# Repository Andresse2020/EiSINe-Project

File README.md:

# Raspberry Pi License Plate Detection System

Real-time license plate detection system for Raspberry Pi with camera support. Detects license plates using YOLO, designed with a clean layered architecture for easy maintenance and hardware portability.

---

## 📑 Table of Contents

- [Project Overview](#-project-overview)
- [Current Status](#-current-status)
- [Architecture](#️-architecture)
- [Project Structure](#-project-structure)
- [Installation](#-installation)
- [Configuration](#️-configuration)
- [Usage](#-usage)
- [Key Components](#-key-components-explained)
- [Development Guidelines](#️-development-guidelines)
- [Testing](#-testing)
- [Troubleshooting](#-troubleshooting)
- [Requirements](#-requirements-summary)
- [Roadmap](#️-roadmap)
- [Contributing](#-contributing)
- [License](#-license)

---

## 🎯 Project Overview

This system captures video frames from a camera, detects license plates in real-time using YOLO object detection, and provides a foundation for future OCR integration. The architecture is designed to run identically on both **PC (development)** and **Raspberry Pi (production)** by simply changing a configuration parameter.

### Key Features

- **Real-time detection**: YOLO-based license plate detection with confidence scoring
- **Hardware abstraction**: Same code runs on PC and Raspberry Pi
- **Multi-driver support**: Easy camera backend switching via factory pattern
- **Thread-safe processing**: Concurrent frame capture and analysis
- **Headless compatible**: No display required for production deployment
- **Modular architecture**: Clean separation of concerns across layers

---

## ✅ Current Status

### Implemented

- ✅ **License plate detection** (YOLO-based object detection)
- ✅ **Multi-driver camera abstraction** (OpenCV implemented, Picamera2 ready)
- ✅ **Service-oriented architecture** (Service → Control → App)
- ✅ **Thread-safe frame processing pipeline**
- ✅ **Bounding box visualization** with confidence scores
- ✅ **Frame buffering service** for non-blocking capture
- ✅ **ROI extraction service** (foundation for plate cropping)
- ✅ **Preprocessing service** (image enhancement pipeline)

### Not Yet Implemented

- ⏳ **OCR** (Optical Character Recognition for reading plate text)
- ⏳ **Plate extraction refinement** (precise plate cropping)
- ⏳ **Database/logging system** (result persistence)
- ⏳ **Web interface** (remote monitoring dashboard)
- ⏳ **Picamera2 driver** (native Raspberry Pi Camera Module support)

---

## 🏗️ Architecture

### Layered Architecture Diagram

```
┌─────────────────────────────────────────────────────────────────────┐
│                           APP LAYER                                 │
│                           main.py                                   │
│               (User interface, display logic, entry point)          │
└────────────────────────────┬────────────────────────────────────────┘
                             │
┌────────────────────────────▼────────────────────────────────────────┐
│                         CONTROL LAYER                               │
│                        lpd_control.py                               │
│          (Pipeline orchestration, threading, business workflow)     │
└────────────────────────────┬────────────────────────────────────────┘
                             │
┌────────────────────────────▼────────────────────────────────────────┐
│                         SERVICE LAYER                               │
│  ┌──────────────────┐  ┌──────────────────┐  ┌──────────────────┐   │
│  │  Camera Service  │  │ YOLO Detector    │  │  Preprocess      │   │
│  │  (Frame buffer)  │  │ Service          │  │  Service         │   │
│  └──────────────────┘  └──────────────────┘  └──────────────────┘   │
│  ┌──────────────────┐  ┌──────────────────┐                         │
│  │ ROI Extraction   │  │  OCR Service     │                         │
│  │ Service          │  │  (Future)        │                         │
│  └──────────────────┘  └──────────────────┘                         │
│         (Reusable components: ML, image processing, I/O)            │
└────────────────────────────┬────────────────────────────────────────┘
                             │
┌────────────────────────────▼────────────────────────────────────────┐
│                       INTERFACE LAYER                               │
│                    camera_interface.py (ABC)                        │
│          (Abstract contract defining camera driver behavior)        │
└────────────────────────────┬────────────────────────────────────────┘
                             │
               ┌─────────────┴─────────────┐
               │                           │
 ┌─────────────▼──────────┐    ┌───────────▼──────────┐
 │   DRIVER LAYER         │    │   DRIVER LAYER       │
 │  opencv_camera.py      │    │  picamera2_camera.py │
 │  (USB/CSI via V4L2)    │    │  (Pi CSI - Future)   │
 │  Cross-platform        │    │  Native Raspberry Pi │
 └────────────────────────┘    └──────────────────────┘

┌─────────────────────────────────────────────────────────────────────┐
│                         CONFIG LAYER                                │
│                      camera_factory.py                              │
│          (Runtime driver selection and instantiation)               │
└─────────────────────────────────────────────────────────────────────┘
```

### Data Flow Pipeline

```
┌──────────────┐   ┌────────────────┐   ┌────────────────┐   ┌──────────┐
│   Camera     │──▶│    Camera      │──▶│      LPD       │──▶│   App    │
│   Driver     │   │    Service     │   │    Control     │   │  Layer   │
└──────────────┘   └────────────────┘   └────────────────┘   └──────────┘
      │                   │                     │                   │
  Hardware           Frame Buffer          YOLO Pipeline        Display
  Capture            (Thread-safe)         • Detection           Results
  (cv2.read)         • Latest frame        • ROI Extract
                     • Non-blocking        • Preprocess
                                          • Overlay
```

**Detailed Flow:**

1. **Camera Driver** (`opencv_camera.py`)
   - Captures raw frames from hardware via OpenCV
   - Returns normalized `Frame` objects

2. **Camera Service** (`camera_service.py`)
   - Runs background thread for continuous capture
   - Buffers latest frame in thread-safe manner
   - Converts `Frame` → `ImageFrame` for upper layers

3. **LPD Control** (`lpd_control.py`)
   - Pulls frames from Camera Service (non-blocking)
   - Runs detection pipeline:
     - YOLO detection → bounding boxes + confidence
     - ROI extraction (optional plate cropping)
     - Preprocessing (optional image enhancement)
     - Debug overlay rendering
   - Stores results thread-safely

4. **App Layer** (`main.py`)
   - Retrieves latest detection results
   - Displays frames with overlays
   - Handles user input (quit, pause, etc.)

---

## 📁 Project Structure

```
raspberry-lpd/
│
├── Software/
│   │
│   ├── App/
│   │   └── main.py                          # Application entry point
│   │
│   ├── Control/
│   │   └── lpd_control.py                   # Detection pipeline controller
│   │
│   ├── Service/
│   │   ├── camera_service.py                # Frame buffering service
│   │   ├── yolo_detector_service.py         # YOLO inference wrapper
│   │   ├── roi_extraction_service.py        # Plate region extraction
│   │   ├── plate_preprocess_service.py      # Image preprocessing
│   │   ├── ocr_service.py                   # OCR (placeholder)
│   │   └── ML_Models/
│   │       ├── license_plate_detector.pt    # YOLO weights (required)
│   │       └── yolov8n.pt                   # Optional backup model
│   │
│   ├── Interface/
│   │   └── camera_interface.py              # Abstract camera contract (ABC)
│   │
│   ├── Drivers/
│   │   └── opencv_camera.py                 # OpenCV camera implementation
│   │
│   ├── Config/
│   │   └── camera_factory.py                # Driver selection factory
│   │
│   ├── Tests/
│   │   ├── test_camera.py                   # Driver unit tests
│   │   └── test_camera_service.py           # Service layer tests
│   │
│   └── Tools/
│       └── debug_display.py                 # Debugging utilities
│
├── launch.sh                                # Startup script (source to load aliases)
├── setup.py                                 # Package configuration
└── README.md                                # This file
```

### Directory Responsibilities

| Directory | Purpose |
|-----------|---------|
| `App/` | User-facing application logic, entry points |
| `Control/` | Business workflows, pipeline orchestration |
| `Service/` | Reusable components (ML models, image processing, I/O) |
| `Interface/` | Abstract contracts for hardware abstraction |
| `Drivers/` | Concrete hardware implementations |
| `Config/` | Configuration files, factory patterns |
| `Tests/` | Unit and integration tests |
| `Tools/` | Development and debugging utilities |

---

## 🔧 Installation

### Development Environment (PC)

**Supported OS:** Linux, macOS, Windows

```bash
# 1. Clone repository
git clone https://github.com/Andresse2020/EiSINe-Project
cd EiSINe-Project

# 2. Ensure pip is installed
python3 -m ensurepip --upgrade
python3 -m pip install --upgrade pip

# 3. Create virtual environment (recommended)
python3 -m venv venv
source venv/bin/activate          # Linux/macOS
# venv\Scripts\activate           # Windows

# 4. Install dependencies
pip install numpy
pip install opencv-python
pip install ultralytics           # YOLO

# 5. Verify installation
python3 -c "import cv2; print('OpenCV:', cv2.__version__)"
python3 -c "import ultralytics; print('YOLO: OK')"
```

### Production Environment (Raspberry Pi)

**Tested on:** Raspberry Pi OS (Bullseye/Bookworm)

```bash
# 1. Update system
sudo apt update && sudo apt upgrade -y

# 2. Install system dependencies
sudo apt install -y python3-opencv python3-pip

# 3. Install Python packages
pip3 install ultralytics numpy

# Optional: Enable Raspberry Pi Camera Module (CSI)
sudo apt install -y python3-picamera2

# 4. Clone repository
git clone https://github.com/Andresse2020/EiSINe-Project
cd EiSINe-Project

# 5. Verify installation
python3 -c "import cv2; print('OpenCV:', cv2.__version__)"
```

### YOLO Model Setup

The system requires a trained YOLO model for license plate detection:

```bash
# Ensure the model file exists at:
Software/Service/ML_Models/license_plate_detector.pt

# If you need to train your own model, see:
# https://docs.ultralytics.com/modes/train/
```

---

## ⚙️ Configuration

### Camera Driver Selection

The **only** configuration needed to switch between PC and Raspberry Pi is in `Software/Config/camera_factory.py`:

```python
# ============================================================
# GLOBAL HARDWARE CONFIGURATION
# ============================================================

# Select active camera driver
# Options:
#   - "Software.Drivers.opencv_camera.OpenCVCamera"       (USB, V4L2)
#   - "Software.Drivers.picamera2_camera.Picamera2Camera" (Pi CSI - future)
ACTIVE_CAMERA_DRIVER = "Software.Drivers.opencv_camera.OpenCVCamera"

# Hardware parameters
CAMERA_HARDWARE_CONFIG = {
    "device_index": 0,                    # /dev/video0 (Linux) or index 0
    "default_resolution": (640, 480),     # Lower for Raspberry Pi performance
    "default_framerate": 30.0,            # FPS target
}
```

### Configuration Examples

#### For PC Development (USB Camera)
```python
ACTIVE_CAMERA_DRIVER = "Software.Drivers.opencv_camera.OpenCVCamera"
CAMERA_HARDWARE_CONFIG = {
    "device_index": 0,              # First USB camera
    "default_resolution": (1280, 720),
    "default_framerate": 30.0,
}
```

#### For Raspberry Pi (USB Camera)
```python
ACTIVE_CAMERA_DRIVER = "Software.Drivers.opencv_camera.OpenCVCamera"
CAMERA_HARDWARE_CONFIG = {
    "device_index": 0,              # /dev/video0
    "default_resolution": (640, 480),  # Lower resolution for performance
    "default_framerate": 15.0,         # Reduced FPS
}
```

#### For Raspberry Pi (CSI Camera - Future)
```python
ACTIVE_CAMERA_DRIVER = "Software.Drivers.picamera2_camera.Picamera2Camera"
CAMERA_HARDWARE_CONFIG = {
    "device_index": 0,
    "default_resolution": (1640, 1232),
    "default_framerate": 30.0,
}
```

---

## 🚀 Usage

### Basic Operation

```bash
# Method 1: Using launch script (loads aliases)
cd EiSINe-Project/Software
source launch.sh     # Once the launch.sh file is succefuly executed, you can run "run_app" and "show_video" in any directory.
run_app              # Launch main detection application
show_video           # Launch debug video display tool

# Method 2: Direct Python execution
cd EiSINe-Project
python3 -m Software.App.main
python3 -m Software.Tools.debug_display

# Method 3: From project root
cd EiSINe-Project
python3 -m Software.App.main
```

### Launch Script Details

The `launch.sh` script provides convenient aliases:

```bash
#!/bin/bash
# Load aliases into current shell
cd EiSINe-Project/Software
source launch.sh

# Available commands:
run_app      # Runs the license plate detection system
show_video   # Runs the debug video display utility
```

**Important:** Use `source launch.sh` (or `. launch.sh`) instead of `./launch.sh` to load aliases into your current shell session.

### Expected Console Output

```
🔍 [DebugDisplay] Starting viewer...
📡 CameraService started.
🧠 LPDControl started.

...

Press 'q' to quit
```

### Keyboard Controls

| Key | Action |
|-----|--------|
| `q` | Quit application |
| `p` | Pause/Resume detection |
| `s` | Save current frame |

### Running Tests

```bash
# Test camera driver
cd EiSINe-Project/Software
python3 -m Software.Tests.test_camera

# Test camera service
cd EiSINe-Project/Software
python3 -m Software.Tests.test_camera_service
```

---

## 🔍 Key Components Explained

### 1. `camera_interface.py` (Interface Layer)

**Purpose:** Defines the abstract contract that all camera drivers must implement.

**Key Methods:**
- `open(config)` — Initialize camera hardware
- `close()` — Release camera resources
- `start_stream()` — Begin continuous capture
- `stop_stream()` — End continuous capture
- `read(timeout)` — Capture a single frame
- `set_config(config)` — Apply camera settings (resolution, FPS, etc.)
- `capabilities()` — Query backend features

**Why it matters:** Upper layers only depend on this interface, never on concrete drivers.

---

### 2. `opencv_camera.py` (Driver Layer)

**Purpose:** Concrete implementation using OpenCV's `cv2.VideoCapture`.

**Features:**
- Works with USB cameras via V4L2 (Linux)
- Cross-platform support (Windows, macOS, Linux)
- Implements full `CameraInterface` contract
- Thread-safe frame acquisition

**Example Usage:**
```python
from Software.Drivers.opencv_camera import OpenCVCamera

cam = OpenCVCamera(device_index=0)
cam.open()
cam.start_stream()
frame = cam.read()  # Returns Frame object
cam.stop_stream()
cam.close()
```

---

### 3. `camera_service.py` (Service Layer)

**Purpose:** Provides thread-safe frame buffering with non-blocking access.

**Features:**
- Background thread continuously captures frames
- Stores latest frame in locked buffer
- Converts `Frame` → `ImageFrame` (simplified data structure)
- Non-blocking `get_latest()` method

**Why it matters:** Decouples frame capture from processing, preventing pipeline blocking.

**Example Usage:**
```python
from Software.Service.camera_service import CameraService

service = CameraService(camera_driver)
service.start()

# Non-blocking access
latest = service.get_latest()  # Returns ImageFrame or None
```

---

### 4. `yolo_detector_service.py` (Service Layer)

**Purpose:** Wraps YOLO model for license plate detection.

**Features:**
- Loads YOLO model from `.pt` file
- Runs inference on images
- Returns bounding boxes sorted by confidence

**Example Usage:**
```python
from Software.Service.yolo_detector_service import YoloDetectorService

detector = YoloDetectorService("path/to/model.pt")
detections = detector.detect(image)  # Returns [(x, y, w, h, conf), ...]
```

---

### 5. `lpd_control.py` (Control Layer)

**Purpose:** Orchestrates the complete detection pipeline.

**Pipeline Steps:**
1. Pull frame from Camera Service
2. Run YOLO detection
3. Extract ROI (optional)
4. Preprocess plate image (optional)
5. Draw debug overlay
6. Store results thread-safely

**Features:**
- Runs in background thread
- Thread-safe result storage
- Configurable processing steps

**Example Usage:**
```python
from Software.Control.lpd_control import LPDControl

controller = LPDControl(camera_service)
controller.start()

# Retrieve latest detection
result = controller.get_latest_result()  # { "bbox": (x,y,w,h), "confidence": 0.89, ... }
frame = controller.get_latest_frame()    # Processed frame with overlay
```

---

### 6. `camera_factory.py` (Config Layer)

**Purpose:** Centralized factory for driver instantiation.

**How it works:**
1. Reads `ACTIVE_CAMERA_DRIVER` from config
2. Dynamically imports driver class
3. Instantiates with `CAMERA_HARDWARE_CONFIG`
4. Validates implementation at runtime

**Example Usage:**
```python
from Software.Config.camera_factory import CameraFactory

# Returns concrete driver based on config
camera = CameraFactory.create()  # Returns OpenCVCamera or Picamera2Camera

# Upper layers only see CameraInterface
camera.open()
camera.start_stream()
```

**Why it matters:** Single source of truth for hardware selection. No conditional imports scattered across codebase.

---

## 🛠️ Development Guidelines

### Architecture Rules

1. **Never import drivers directly** — Always use `CameraFactory`
2. **Respect layer boundaries:**
   - App → Control → Service → Interface → Driver
   - Lower layers never import from upper layers
3. **Keep services stateless** or thread-safe
4. **No hardware logic** in Control/Service layers

### Adding a New Camera Driver

**Steps:**

1. Create `Software/Drivers/my_camera.py`
2. Inherit from `CameraInterface`
3. Implement all abstract methods
4. Update `camera_factory.py`
5. Write tests

**Example Template:**

```python
from Software.Interface.camera_interface import (
    CameraInterface,
    CameraConfig,
    Frame,
    CameraOpenError,
)

class MyCamera(CameraInterface):
    def __init__(self, device_index=0, **kwargs):
        super().__init__()
        self._device = device_index
        self._name = "MyCamera"

    def open(self, config=None):
        # Initialize hardware
        self._is_open = True

    def close(self):
        # Release hardware
        self._is_open = False

    def start_stream(self):
        self._is_streaming = True

    def stop_stream(self):
        self._is_streaming = False

    def read(self, timeout=2.0):
        # Capture and return Frame
        pass

    def flush(self):
        pass

    def capture(self, path=None):
        pass

    def set_config(self, config):
        pass

    def capabilities(self):
        return {}
```

### Adding a New Service

**Guidelines:**

1. Create `Software/Service/my_service.py`
2. Keep it stateless or use locks for thread safety
3. No direct hardware access (use existing services)
4. Write unit tests in `Software/Tests/`

**Example:**

```python
class MyService:
    def __init__(self):
        # Initialize resources
        pass

    def process(self, data):
        # Stateless processing
        return result
```

---

## 🧪 Testing

### Running Tests

```bash
# Run all tests
python3 -m pytest Software/Tests/ -v

# Run specific test file
python3 -m pytest Software/Tests/test_camera.py -v

# Run with coverage
pip install pytest-cov
python3 -m pytest Software/Tests/ --cov=Software --cov-report=html
```

### Manual Testing

```bash
# Test camera access
python3 -c "from Software.Config.camera_factory import CameraFactory; \
            cam = CameraFactory.create(); \
            cam.open(); \
            print('Camera OK')"

# Test YOLO model
python3 -c "from Software.Service.yolo_detector_service import YoloDetectorService; \
            detector = YoloDetectorService('Software/Service/ML_Models/license_plate_detector.pt'); \
            print('Model loaded OK')"
```

---

## 🐛 Troubleshooting

### Camera Not Detected

**Problem:** Camera fails to open

```bash
# Check available video devices
ls /dev/video*

# Test OpenCV access
python3 -c "import cv2; cap = cv2.VideoCapture(0); print('Opened:', cap.isOpened())"

# Check permissions
groups  # Should include 'video'
sudo usermod -a -G video $USER  # Add user to video group
# Logout and login again
```

### Low FPS on Raspberry Pi

**Solutions:**

1. **Reduce resolution:**
   ```python
   # In camera_factory.py
   "default_resolution": (320, 240),  # Even lower
   ```

2. **Lower framerate:**
   ```python
   "default_framerate": 10.0,
   ```

3. **Use lighter YOLO model:**
   - Replace `license_plate_detector.pt` with `yolov8n.pt` (nano version)

4. **Disable debug overlays:**
   ```python
   # In lpd_control.py, comment out:
   # self._draw_overlay(processed, x, y, w, h, conf)
   ```

### Permission Denied on `/dev/video0`

```bash
# Add user to video group
sudo usermod -a -G video $USER

# Or run with sudo (not recommended for production)
sudo python3 Software/App/main.py
```

### YOLO Model Not Found

```bash
# Check model path
ls Software/Service/ML_Models/license_plate_detector.pt

# If missing, download or train your own
# See: https://docs.ultralytics.com/
```

### Import Errors

```bash
# Ensure you're in project root
cd raspberry-lpd

# Check PYTHONPATH
export PYTHONPATH="${PYTHONPATH}:$(pwd)"

# Or install as package
pip install -e .
```

---

## 📦 Requirements Summary

### Hardware Requirements

| Component | Minimum | Recommended |
|-----------|---------|-------------|
| Raspberry Pi | Pi 3B | Pi 4 (4GB+) |
| Camera | USB 2.0 webcam | Pi Camera Module v2/v3 |
| RAM | 1GB | 2GB+ |
| SD Card | 8GB | 16GB+ (Class 10) |
| Power Supply | 2.5A | 3A (official) |

### Software Requirements

**Python:** 3.8 or higher

**Core Dependencies:**
- `opencv-python` (4.x) — Image processing and camera I/O
- `ultralytics` — YOLO object detection
- `numpy` — Numerical operations

**Optional Dependencies:**
- `picamera2` — Raspberry Pi Camera Module support (future)
- `pytest` — Unit testing
- `tesseract` / `easyocr` — OCR (future implementation)

### Operating Systems

| OS | Status |
|----|--------|
| Raspberry Pi OS (Bullseye/Bookworm) | ✅ Fully supported |
| Ubuntu 20.04+ | ✅ Supported |
| Debian 11+ | ✅ Supported |
| macOS | ⚠️ Development only |
| Windows 10+ | ⚠️ Development only |

---

## 🗺️ Roadmap

### Phase 1: Core Detection (Current)
- [x] YOLO-based license plate detection
- [x] OpenCV camera driver
- [x] Layered architecture
- [x] Thread-safe processing pipeline

### Phase 2: OCR Integration
- [ ] Implement OCR service (Tesseract or EasyOCR)
- [ ] Plate text extraction and validation
- [ ] Result confidence scoring
- [ ] Multi-language support

### Phase 3: Hardware Expansion
- [ ] Picamera2 driver for Raspberry Pi Camera Module
- [ ] Multi-camera support
- [ ] Hardware acceleration (Coral TPU, Neural Compute Stick)

### Phase 4: Data Persistence
- [ ] SQLite/PostgreSQL database integration
- [ ] Detection history logging
- [ ] Image archiving system
- [ ] Export to CSV/JSON

### Phase 5: Remote Access
- [ ] REST API (Flask/FastAPI)
- [ ] Web dashboard (React/Vue)
- [ ] Real-time monitoring
- [ ] Mobile app support

### Phase 6: Optimization
- [ ] Performance tuning for Pi Zero
- [ ] Battery power optimization
- [ ] Edge processing (on-device analytics)
- [ ] Docker containerization

### Future Enhancements
- [ ] Vehicle tracking and counting
- [ ] Parking violation detection
- [ ] Integration with access control systems
- [ ] Cloud sync and backup

---

## 🤝 Contributing

Contributions are welcome! Please follow these guidelines:

### Development Workflow

1. **Fork the repository**
2. **Create a feature branch:**
   ```bash
   git checkout -b feature/my-new-feature
   ```
3. **Follow the architecture:**
   - Respect layer boundaries
   - Use existing abstractions
   - Keep drivers isolated
4. **Write tests:**
   - Unit tests for new services
   - Integration tests for workflows
5. **Update documentation:**
   - Code comments
   - README updates if needed
6. **Submit pull request:**
   - Clear description of changes
   - Reference related issues

### Code Style

- **Python:** Follow PEP 8
- **Imports:** Use absolute imports (`from Software.Service...`)
- **Type hints:** Use where appropriate
- **Docstrings:** Google-style for public APIs

### Architecture Principles

✅ **DO:**
- Use `CameraFactory` for hardware access
- Keep services stateless or thread-safe
- Write unit tests for new components
- Follow layer separation strictly

❌ **DON'T:**
- Import drivers directly in upper layers
- Add hardware logic to Control/Service layers
- Create circular dependencies
- Modify interfaces without updating all implementations

---

## 📄 License

This project is licensed under the MIT License - see the [LICENSE](LICENSE) file for details.

```
MIT License

Copyright (c) 2024 [Your Name]

Permission is hereby granted, free of charge, to any person obtaining a copy
of this software and associated documentation files (the "Software"), to deal
in the Software without restriction, including without limitation the rights
to use, copy, modify, merge, publish, distribute, sublicense, and/or sell
copies of the Software, and to permit persons to whom the Software is
furnished to do so, subject to the following conditions:

The above copyright notice and this permission notice shall be included in all
copies or substantial portions of the Software.

THE SOFTWARE IS PROVIDED "AS IS", WITHOUT WARRANTY OF ANY KIND, EXPRESS OR
IMPLIED, INCLUDING BUT NOT LIMITED TO THE WARRANTIES OF MERCHANTABILITY,
FITNESS FOR A PARTICULAR PURPOSE AND NONINFRINGEMENT. IN NO EVENT SHALL THE
AUTHORS OR COPYRIGHT HOLDERS BE LIABLE FOR ANY CLAIM, DAMAGES OR OTHER
LIABILITY, WHETHER IN AN ACTION OF CONTRACT, TORT OR OTHERWISE, ARISING FROM,
OUT OF OR IN CONNECTION WITH THE SOFTWARE OR THE USE OR OTHER DEALINGS IN THE
SOFTWARE.
```

---

## 📞 Contact & Support

### Questions or Issues?

- **GitHub Issues:** [https://github.com/Andresse2020/EiSINe-Project](https://github.com/Andresse2020/EiSINe-Project)
- **Email:** brisel.bassinga@gmail.com
- **Documentation:** See inline code comments and docstrings

### Useful Links

- [Ultralytics YOLO Documentation](https://docs.ultralytics.com/)
- [OpenCV Python Tutorials](https://docs.opencv.org/4.x/d6/d00/tutorial_py_root.html)
- [Raspberry Pi Documentation](https://www.raspberrypi.com/documentation/)
- [Picamera2 Manual](https://datasheets.raspberrypi.com/camera/picamera2-manual.pdf)

---

## 🙏 Acknowledgments

- **Ultralytics** for YOLO implementation
- **OpenCV** community for image processing tools
- **Raspberry Pi Foundation** for accessible hardware

---

## 📝 Notes for Continuators

### Critical Information

1. **Hardware Abstraction:**
   - ALL camera hardware logic is in `Drivers/` directory
   - NEVER modify other layers for hardware changes
   - Use `CameraFactory` exclusively for instantiation

2. **Model Path:**
   - YOLO model path is hardcoded in `yolo_detector_service.py`
   - Update if you move the `ML_Models/` directory

3. **Headless Operation:**
   - System designed for headless deployment
   - No GUI dependencies required
   - Display logic is optional (in `main.py`)

4. **Platform Switching:**
   - To switch between PC and Raspberry Pi: Edit `camera_factory.py` ONLY
   - Everything else remains identical

5. **Thread Safety:**
   - Frame buffer in `CameraService` uses locks
   - Detection results in `LPDControl` use locks
   - Never access shared state without locking

### Quick Start Checklist

- [ ] Install dependencies (see [Installation](#-installation))
- [ ] Place YOLO model in `Software/Service/ML_Models/`
- [ ] Configure camera driver in `camera_factory.py`
- [ ] Test camera access: `ls /dev/video*`
- [ ] Run tests: `pytest Software/Tests/`
- [ ] Load launch script: `source launch.sh`
- [ ] Launch system: `run_app` (or `python3 -m Software.App.main`)

### Launch Script Usage

The `launch.sh` file defines convenient bash aliases but does NOT execute the application directly. Proper usage:

```bash
# ✅ CORRECT: Source the script to load aliases
source launch.sh
# Output: ✅ Launch alias 'run_app and show_video' has been loaded.

# Then use the aliases
run_app         # Launches Software.App.main
show_video      # Launches Software.Tools.debug_display

# ❌ INCORRECT: Running as executable won't load aliases
./launch.sh     # This won't work (aliases only exist in subshell)
```

**Alternative:** You can add `source /path/to/EiSINe-Project/Software/launch.sh` to your `~/.bashrc` to load aliases permanently.

---

**Last Updated:** February 5, 2024  
**Version:** 1.0.0  
**Status:** Active Development

---

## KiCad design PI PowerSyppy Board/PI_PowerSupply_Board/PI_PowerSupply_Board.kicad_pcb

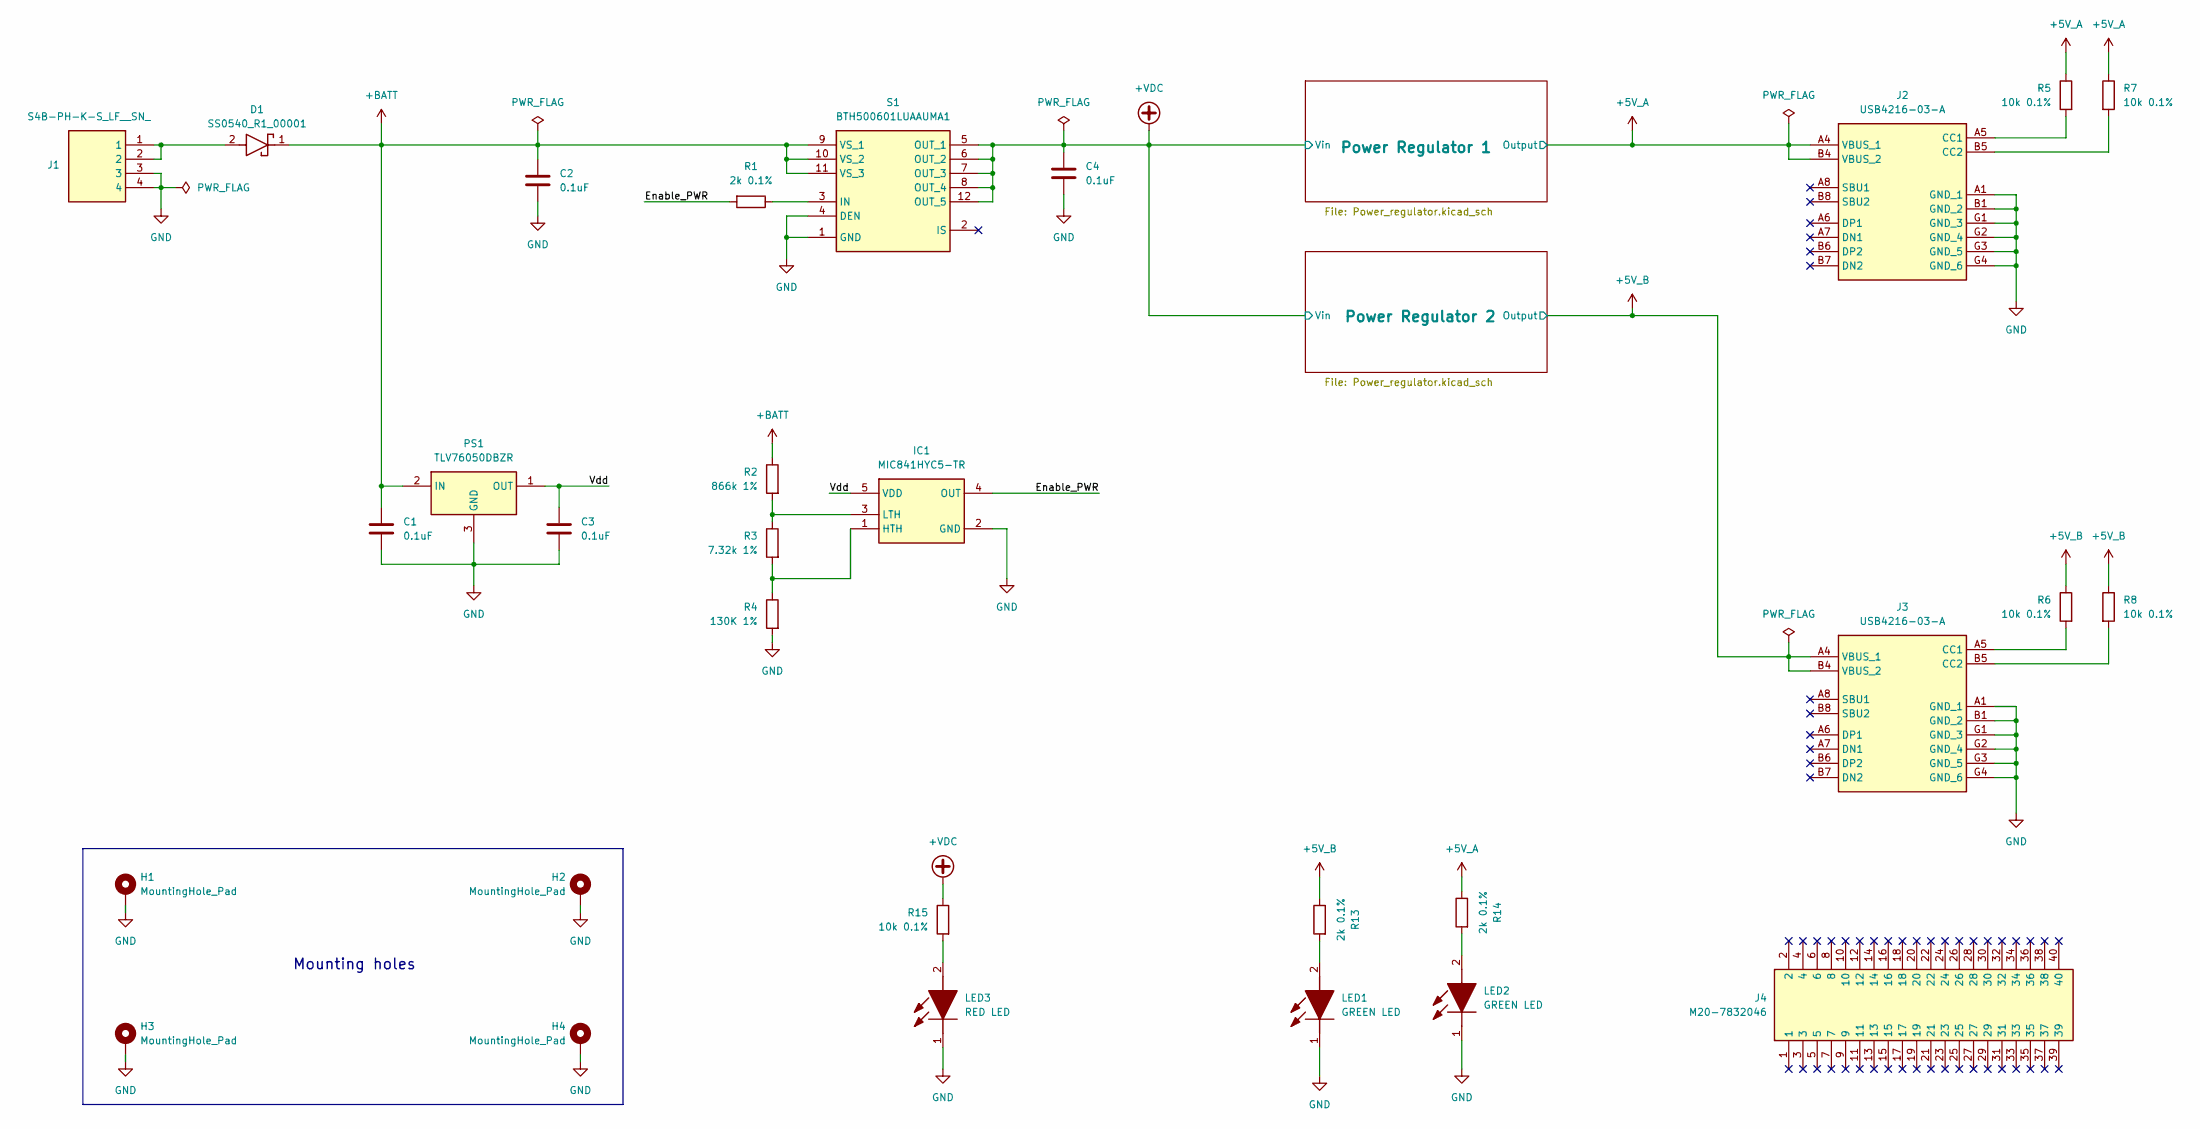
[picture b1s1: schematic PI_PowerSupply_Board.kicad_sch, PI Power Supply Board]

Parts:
C1, C2, C3, C4: 0.1uF; C_0603_1608Metric; Manufacturer_Part_Number CL10B104KB8NNNC
D1: SS0540_R1_00001; SOD3816X135N; Mouser Part Number 241-SS0540_R1_00001
H1, H2, H3, H4: MountingHole_Pad; MountingHole_2.7mm_M2.5_DIN965_Pad_TopBottom
IC1: MIC841HYC5-TR; SOT65P210X110-5N; Mouser Part Number 998-MIC841HYC5TR
J1: S4B-PH-K-S_LF__SN_; Mouser Part Number N/A
J2, J3: USB4216-03-A; USB421603A; Mouser Part Number 640-USB4216-03-A
J4: M20-7832046; RHDR40W65P254_2X20_5120X504X850P; Mouser Part Number 855-M20-7832046
LED1, LED2: GREEN LED; LEDM168X80N; Mouser Part Number 604-APHD1608LZGCK
LED3: RED LED; LEDM168X80N; Manufacturer_Part_Number APHD1608LSURCK
PS1: TLV76050DBZR; SOT95P237X112-3N; Mouser Part Number 595-TLV76050DBZR
R1, R13, R14: 2k 0.1%; R_0603_1608Metric; Manufacturer_Part_Number RT0603BRD072KL
R2: 866k 1%; R_0603_1608Metric; Manufacturer_Part_Number AC0603FR-07866KL
R3: 7.32k 1%; R_0603_1608Metric; Manufacturer_Part_Number RT0603FRE077K32L
R4: 130K 1%; R_0603_1608Metric; Manufacturer_Part_Number RC0603FR-07130KL
R5, R6, R7, R8, R15: 10k 0.1%; R_0603_1608Metric; Manufacturer_Part_Number RT0603BRE0710KL
S1: BTH500601LUAAUMA1; BTS500101LUA; Manufacturer_Part_Number BTH500601LUAAUMA1

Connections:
+5V_A: J2.A4 (VBUS_1), J2.B4 (VBUS_2), R5.1, R7.1, R14.1; also elsewhere on the board
+5V_B: J3.A4 (VBUS_1), J3.B4 (VBUS_2), R6.1, R8.1, R13.1; also elsewhere on the board
+BATT: C1.1, C2.1, D1.1 (K), PS1.2 (IN), R2.1, S1.9 (VS_1), S1.10 (VS_2), S1.11 (VS_3)
+VDC: C4.1, R15.1, S1.5 (OUT_1), S1.6 (OUT_2), S1.7 (OUT_3), S1.8 (OUT_4), S1.12 (OUT_5); also elsewhere on the board
/Enable_PWR: IC1.4 (OUT), R1.2
/Vdd: C3.1, IC1.5 (VDD), PS1.1 (OUT)
GND: C1.2, C2.2, C3.2, C4.2, H1.1, H2.1, H3.1, H4.1, IC1.2 (GND), J1.3, J1.4, J2.A1 (GND_1), J2.B1 (GND_2), J2.G1 (GND_3), J2.G2 (GND_4), J2.G3 (GND_5), J2.G4 (GND_6), J3.A1 (GND_1), J3.B1 (GND_2), J3.G1 (GND_3), J3.G2 (GND_4), J3.G3 (GND_5), J3.G4 (GND_6), LED1.1 (K), LED2.1 (K), LED3.1 (K), PS1.3 (GND), R4.2, S1.1 (GND), S1.4 (DEN); also elsewhere on the board
unnamed: D1.2 (A), J1.1, J1.2
unnamed: IC1.1 (HTH), R3.2, R4.1
unnamed: IC1.3 (LTH), R2.2, R3.1
unnamed: J2.A5 (CC1), R5.2
unnamed: J2.B5 (CC2), R7.2
unnamed: J3.A5 (CC1), R6.2
unnamed: J3.B5 (CC2), R8.2
unnamed: LED1.2 (A), R13.2
unnamed: LED2.2 (A), R14.2
unnamed: LED3.2 (A), R15.2
unnamed: R1.1, S1.3 (IN)

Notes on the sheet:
Mounting holes

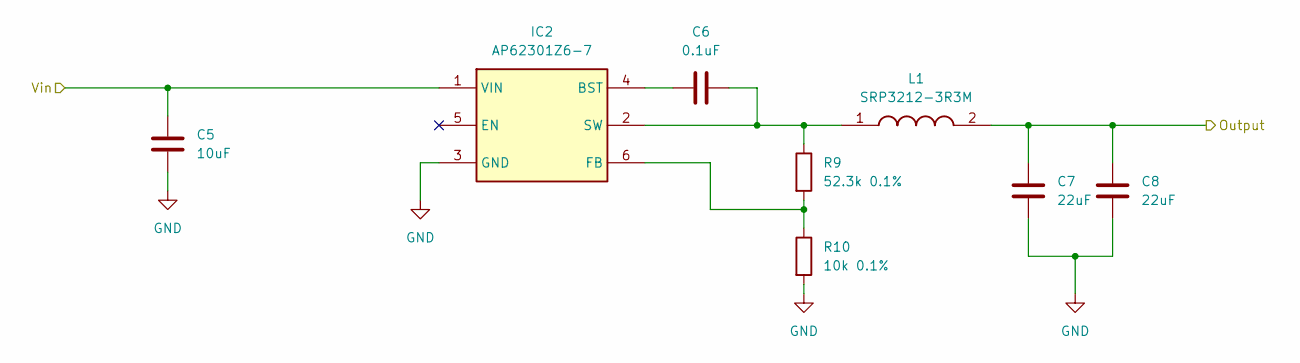
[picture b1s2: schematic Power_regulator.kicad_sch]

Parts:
C5: 10uF; C_1210_3225Metric; Manufacturer_Part_Number CL32B106KMVNNWE
C6: 0.1uF; C_0603_1608Metric; Manufacturer_Part_Number CL10B104KB8NNNC
C7, C8: 22uF; C_1210_3225Metric; Manufacturer_Part_Number CL32B226KAJNNNE
IC2: AP62301Z6-7; SOTFL50P160X60-6N; Mouser Part Number 621-AP62301Z6-7
L1: SRP3212-3R3M; INDC2520X100N; Mouser Part Number 652-SRP3212-3R3M
R9: 52.3k 0.1%; R_0603_1608Metric; Manufacturer_Part_Number RT0603BRD0752K3L
R10: 10k 0.1%; R_0603_1608Metric; Manufacturer_Part_Number RT0603BRE0710KL

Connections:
+5V_B: C7.1, C8.1, L1.2; also elsewhere on the board
+VDC: C5.1, IC2.1 (VIN); also elsewhere on the board
GND: C5.2, C7.2, C8.2, IC2.3 (GND), R10.2; also elsewhere on the board
unnamed: C6.1, IC2.4 (BST)
unnamed: IC2.6 (FB), R9.2, R10.1
unnamed: C6.2, IC2.2 (SW), L1.1, R9.1

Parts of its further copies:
C9: 10uF; C_1210_3225Metric; Manufacturer_Part_Number CL32B106KMVNNWE
C10: 0.1uF; C_0603_1608Metric; Manufacturer_Part_Number CL10B104KB8NNNC
C11, C12: 22uF; C_1210_3225Metric; Manufacturer_Part_Number CL32B226KAJNNNE
IC3: AP62301Z6-7; SOTFL50P160X60-6N; Mouser Part Number 621-AP62301Z6-7
L2: SRP3212-3R3M; INDC2520X100N; Mouser Part Number 652-SRP3212-3R3M
R11: 52.3k 0.1%; R_0603_1608Metric; Manufacturer_Part_Number RT0603BRD0752K3L
R12: 10k 0.1%; R_0603_1608Metric; Manufacturer_Part_Number RT0603BRE0710KL

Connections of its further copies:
+5V_A: C11.1, C12.1, L2.2; also elsewhere on the board
+VDC: C9.1, IC3.1 (VIN); also elsewhere on the board
GND: C9.2, C11.2, C12.2, IC3.3 (GND), R12.2; also elsewhere on the board
unnamed: C10.1, IC3.4 (BST)
unnamed: IC3.6 (FB), R11.2, R12.1
unnamed: C10.2, IC3.2 (SW), L2.1, R11.1

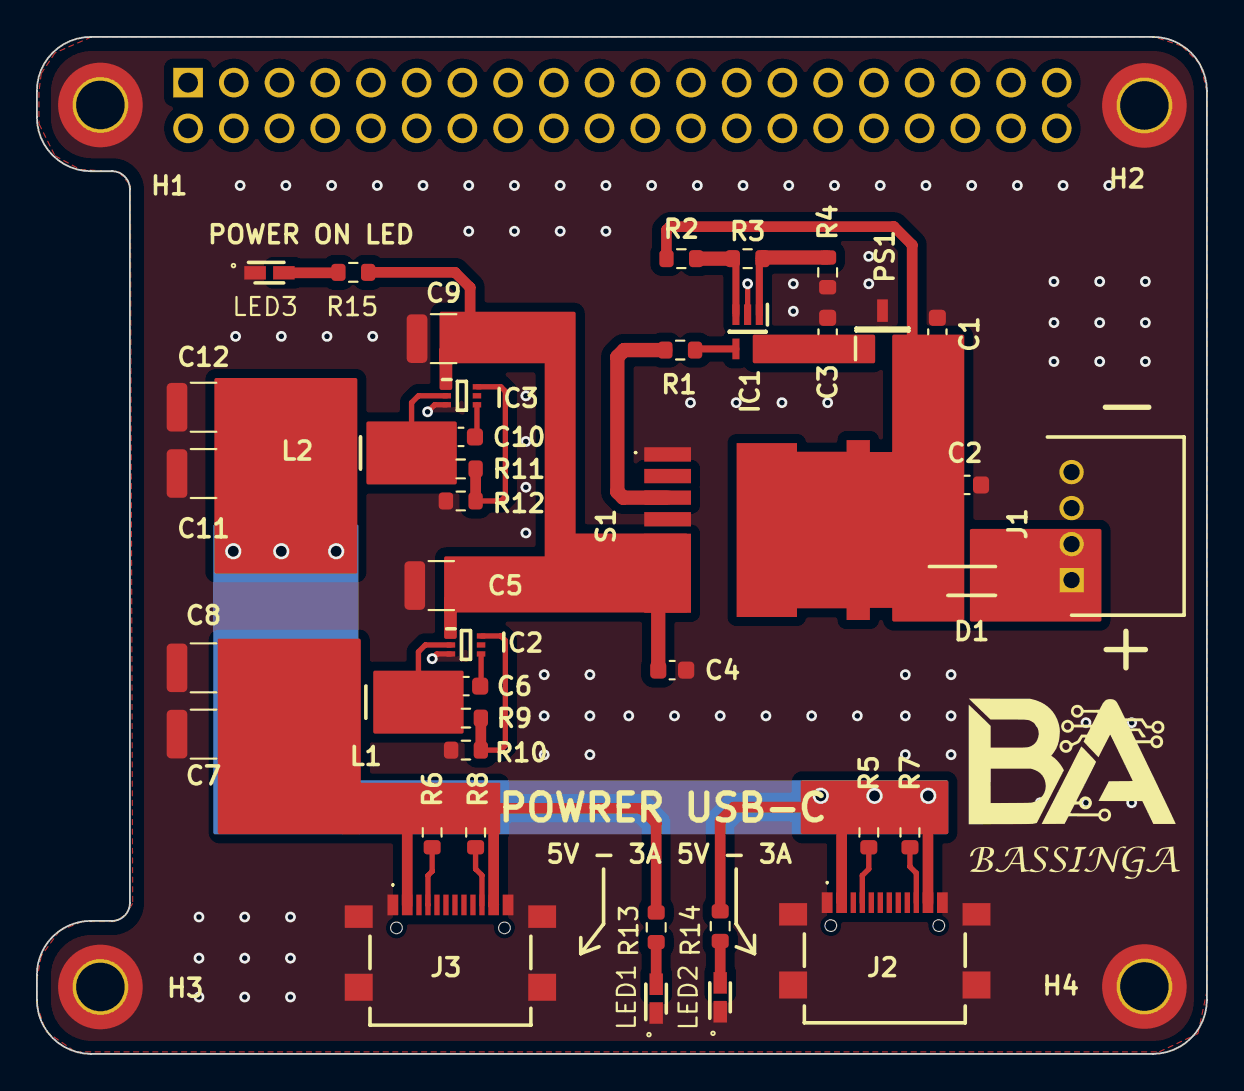
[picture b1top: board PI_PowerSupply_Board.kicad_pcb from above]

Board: 2 copper layers, 65.0 x 56.5 mm, 46 parts (1 on the bottom side), 24 nets.

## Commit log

2025-09-29 Schematic design
2025-09-30 PCB Design
2025-10-18 Calculus file
2025-10-28 Software Architecture Complete
2025-11-18 plate detection implemented
2025-11-19 Image processing
2026-02-05 README.md updated
2026-02-05 README.md update

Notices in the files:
README.md:
Raspberry Pi License Plate Detection System:
[Python 3.8+](https://www.python.org/downloads/)
[OpenCV](https://opencv.org/)
[YOLO](https://github.com/ultralytics/ultralytics)
[License: MIT](LICENSE)
